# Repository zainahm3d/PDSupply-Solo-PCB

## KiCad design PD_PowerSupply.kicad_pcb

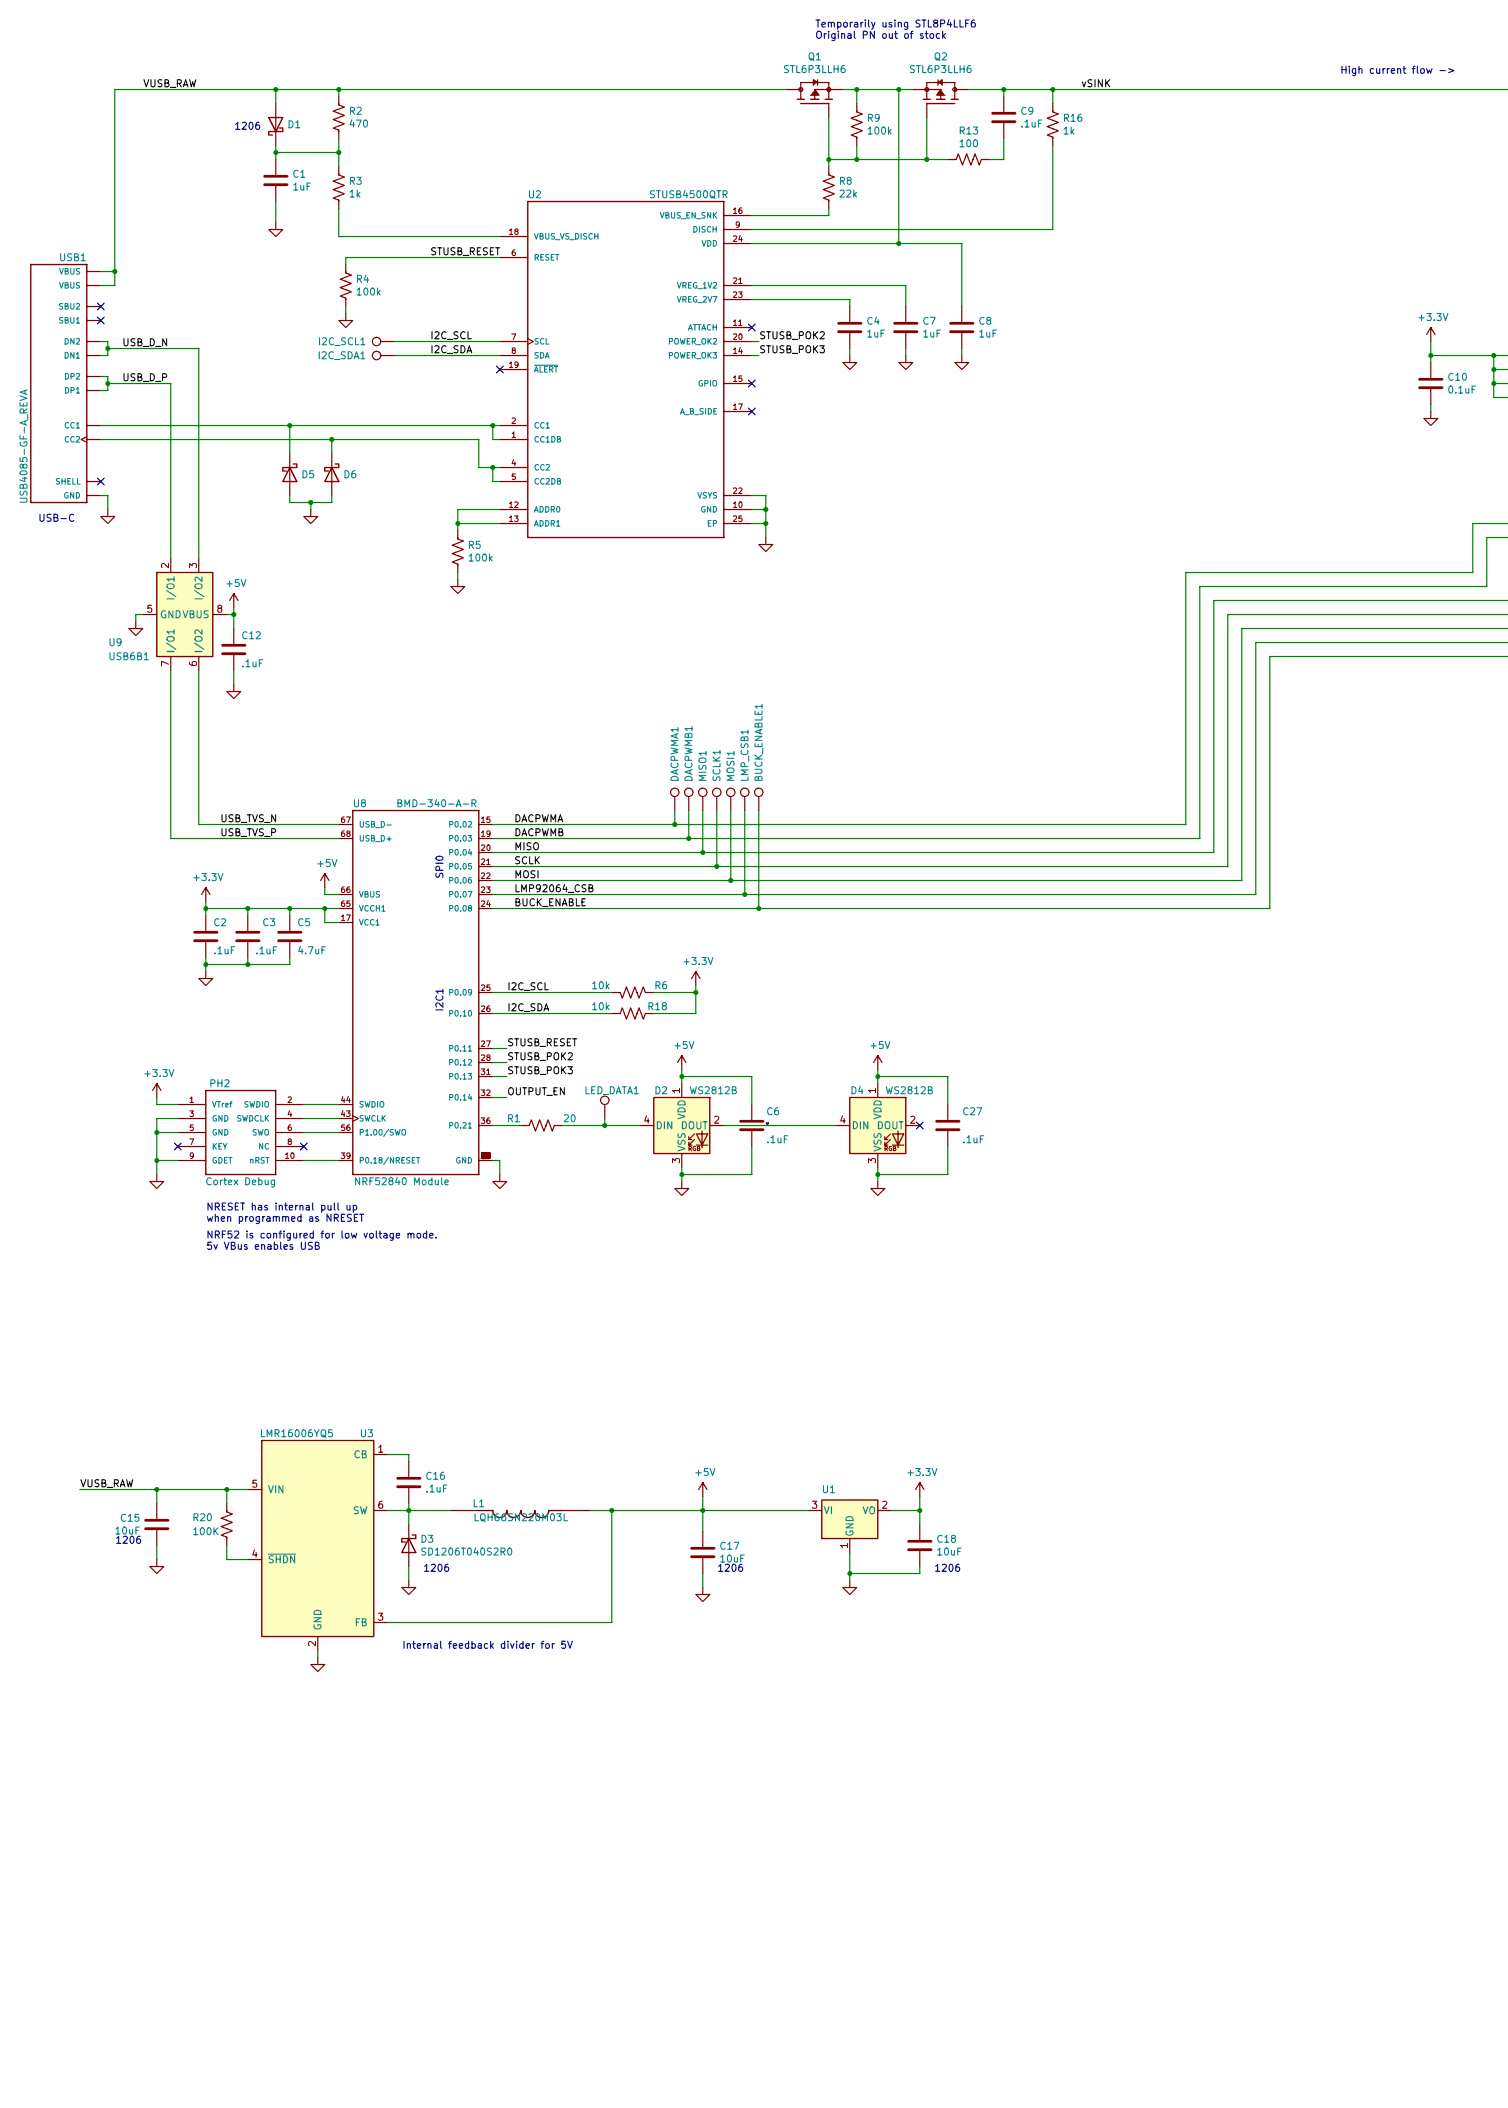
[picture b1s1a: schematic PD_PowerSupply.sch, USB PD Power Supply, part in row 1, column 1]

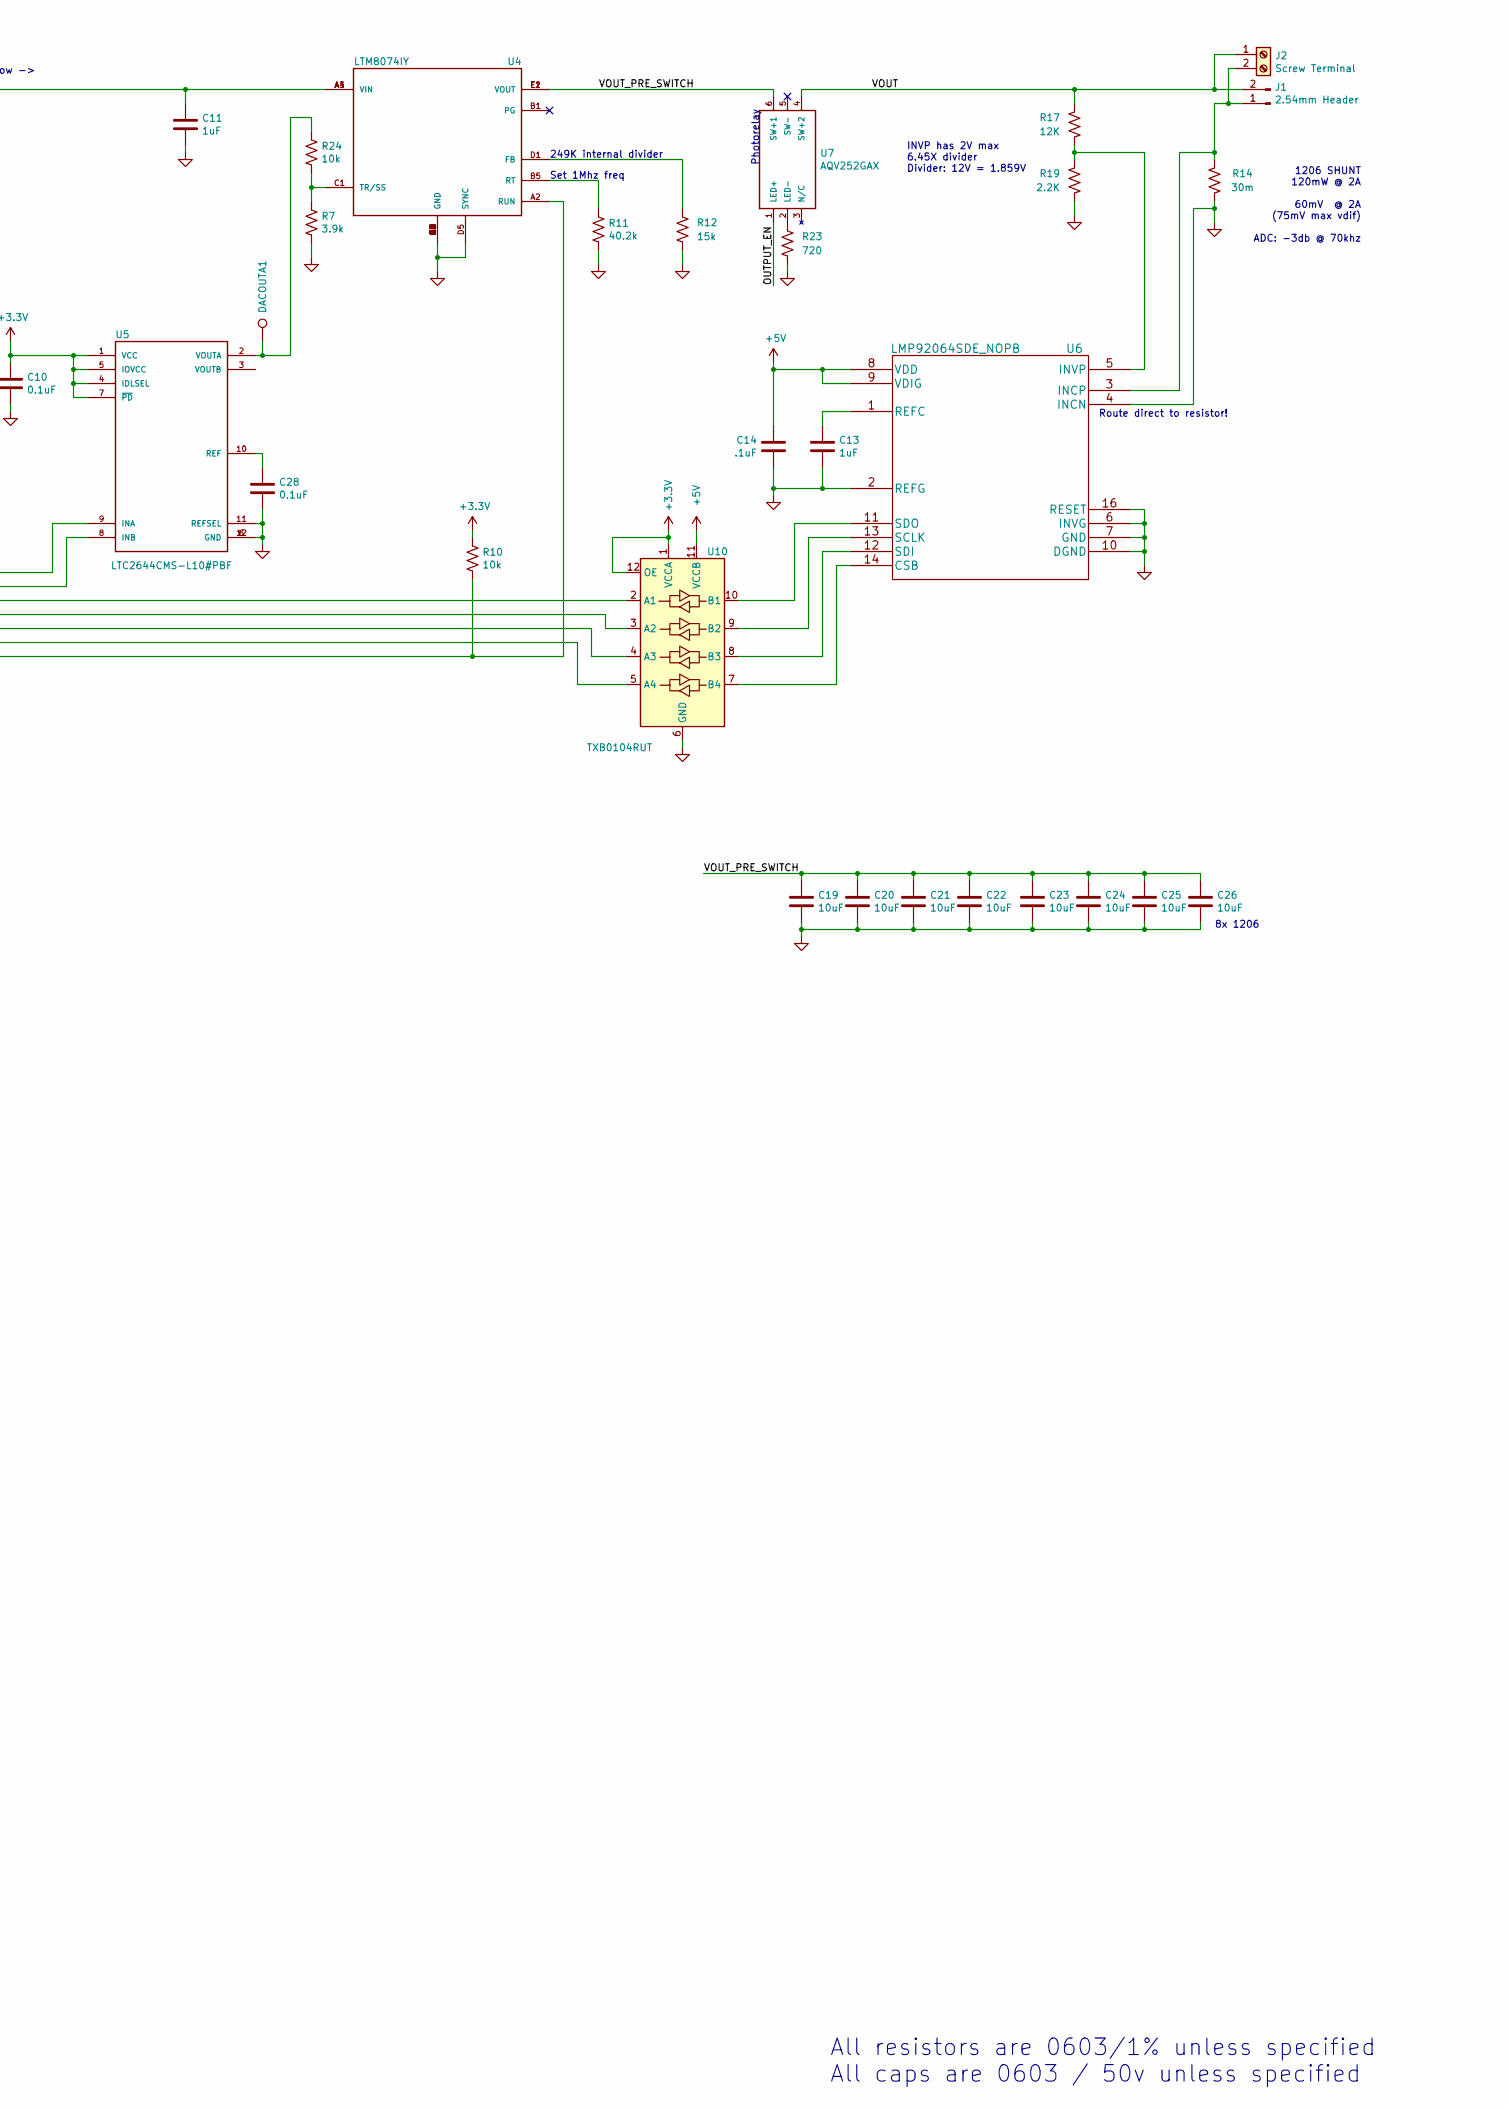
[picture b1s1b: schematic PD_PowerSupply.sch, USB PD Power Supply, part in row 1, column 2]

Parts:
BUCK_ENABLE1: TestPoint; TestPoint_Pad_D1.0mm
C1, C4, C7, C8, C11, C13: 1uF; C_0603_1608Metric
C2, C3, C6, C9, C12, C14, C27: .1uF; C_0603_1608Metric
C5: 4.7uF; C_0603_1608Metric
C10, C28: 0.1uF; C_0603_1608Metric
C15, C17, C18, C19, C20, C21, C22, C23, C24, C25, C26: 10uF; C_1206_3216Metric
C16: .1uF; C_1206_3216Metric
D1: D_Schottky; D_1206_3216Metric_Castellated
D2, D4: WS2812B; LED_WS2812B_PLCC4_5.0x5.0mm_P3.2mm
D3: SD1206T040S2R0; D_1206_3216Metric_Castellated
D5, D6: D_Schottky; D_0603_1608Metric_Castellated
DACOUTA1: TestPoint; TestPoint_Pad_D1.0mm
DACPWMA1: TestPoint; TestPoint_Pad_D1.0mm
DACPWMB1: TestPoint; TestPoint_Pad_D1.0mm
I2C_SCL1, I2C_SDA1: TestPoint; TestPoint_Pad_D1.0mm
J1: 2.54mm Header; PinHeader_1x02_P2.54mm_Horizontal
J2: Screw Terminal; TerminalBlock_Phoenix_MKDS-1,5-2_1x02_P5.00mm_Horizontal
L1: LQH66SN220M03L; IND_LQH66SN220M03L
LED_DATA1: TestPoint; TestPoint_Pad_D1.0mm
LMP_CSB1: TestPoint; TestPoint_Pad_D1.0mm
MISO1: TestPoint; TestPoint_Pad_D1.0mm
MOSI1: TestPoint; TestPoint_Pad_D1.0mm
PH2: FTSH-105-01-L-DV-K; SAMTEC_FTSH-105-01-L-DV-K
Q1, Q2: STL6P3LLH6; TRANS_STL6P3LLH6
R1: 20; R_0603_1608Metric
R2: 470; R_0603_1608Metric
R3, R16: 1k; R_0603_1608Metric
R4, R5, R9: 100k; R_0603_1608Metric
R6, R10, R18, R24: 10k; R_0603_1608Metric
R7: 3.9k; R_0603_1608Metric
R8: 22k; R_0603_1608Metric
R11: 40.2k; R_0603_1608Metric
R12: 15k; R_0603_1608Metric
R13: 100; R_0603_1608Metric
R14: 30m; R_1206_3216Metric
R17: 12K; R_0603_1608Metric
R19: 2.2K; R_0603_1608Metric
R20: 100K; R_0603_1608Metric
R23: 720; R_0603_1608Metric
SCLK1: TestPoint; TestPoint_Pad_D1.0mm
U1: LM1117LD-3.3; SOT-223-3_TabPin2
U2: STUSB4500QTR; QFN50P400X400X90-25N
U3: LMR16006YQ5; SOT-23-6
U4: LTM8074IY; BGA25C65P5X5_400X400X198N
U5: LTC2644CMS-L10#PBF; SOP65P490X110-12N_LTC2644CMS-L10#PBF
U6: LMP92064SDE_NOPB; LMP92064SDE&slash_NOPB
U7: AQV252GAX; SOP6
U8: BMD-340-A-R; RIGADO_BMD-340-A-R
U9: USB6B1; SOIC-8_3.9x4.9mm_P1.27mm
U10: TXB0104RUT; Texas_R_PUQFN-N12
USB1: USB4085-GF-A_REVA; GCT_USB4085-GF-A_REVA

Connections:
+3V3: C2.1, C3.1, C5.1, C10.1, C18.1, PH2.1 (VTref), R6.1, R10.1, R18.1, U1.2 (VO), U5.1 (VCC), U5.4 (IDLSEL), U5.5 (IOVCC), U5.7 (~PD~), U8.17 (VCC1), U8.65 (VCCH1), U10.1 (VCCA), U10.12 (OE)
+5V: C6.1, C12.1, C14.1, C17.1, C27.1, D2.1 (VDD), D4.1 (VDD), L1.2, U1.3 (VI), U3.3 (FB), U6.8 (VDD), U6.9 (VDIG), U8.66 (VBUS), U9.1 (VBUS), U9.8 (VBUS), U10.11 (VCCB)
/BUCK_ENABLE: BUCK_ENABLE1.1, R10.2, U4.A2 (RUN), U8.24 (P0.08)
/DACPWMA: DACPWMA1.1, U5.9 (INA), U8.15 (P0.02)
/DACPWMB: DACPWMB1.1, U5.8 (INB), U8.19 (P0.03)
/I2C_SCL: I2C_SCL1.1, R6.2, U2.7 (SCL), U8.25 (P0.09)
/I2C_SDA: I2C_SDA1.1, R18.2, U2.8 (SDA), U8.26 (P0.10)
/LMP92064_CSB: LMP_CSB1.1, U8.23 (P0.07), U10.5 (A4)
/MISO: MISO1.1, U8.20 (P0.04), U10.2 (A1)
/MOSI: MOSI1.1, U8.22 (P0.06), U10.4 (A3)
/OUTPUT_EN: U7.1 (LED+), U8.32 (P0.14)
/SCLK: SCLK1.1, U8.21 (P0.05), U10.3 (A2)
/STUSB_POK2: U2.20 (POWER_OK2), U8.28 (P0.12)
/STUSB_POK3: U2.14 (POWER_OK3), U8.31 (P0.13)
/STUSB_RESET: R4.1, U2.6 (RESET), U8.27 (P0.11)
/USB_D_N: U9.3 (I/O2), USB1.A7 (DN1), USB1.B7 (DN2)
/USB_D_P: U9.2 (I/O1), USB1.A6 (DP1), USB1.B6 (DP2)
/USB_TVS_N: U8.67 (USB_D-), U9.6 (I/O2)
/USB_TVS_P: U8.68 (USB_D+), U9.7 (I/O1)
/VOUT: J1.2, J2.1, R17.1, U7.4 (SW+2)
/VOUT_PRE_SWITCH: C19.1, C20.1, C21.1, C22.1, C23.1, C24.1, C25.1, C26.1, U4.E1 (VOUT), U4.E2 (VOUT), U7.6 (SW+1)
/VUSB_RAW: C15.2, D1.2 (A), Q1.5_6_7_8 (D), R2.1, R20.1, U3.5 (VIN), USB1.A4 (VBUS), USB1.A9 (VBUS), USB1.B4 (VBUS), USB1.B9 (VBUS)
/vSINK: C9.1, C11.1, Q2.5_6_7_8 (D), R16.2, U4.A3 (VIN), U4.A4 (VIN)
GND: C1.2, C2.2, C3.2, C4.2, C5.2, C6.2, C7.2, C8.2, C10.2, C11.2, C12.2, C13.2, C14.2, C15.1, C17.2, C18.2, C19.2, C20.2, C21.2, C22.2, C23.2, C24.2, C25.2, C26.2, C27.2, C28.2, D2.3 (VSS), D3.2 (A), D4.3 (VSS), D5.2 (A), D6.2 (A), PH2.3 (GND), PH2.5 (GND), PH2.9 (GDET), R4.2, R5.2, R7.2, R11.2, R12.2, R14.2, R19.2, R23.2, U1.1 (GND), U2.10 (GND), U2.22 (VSYS), U2.25 (EP), U3.2 (GND), U4.A1 (GND), U4.A5 (GND), U4.B2 (GND), U4.B3 (GND), U4.B4 (GND), U4.C2 (GND), U4.C3 (GND), U4.C4 (GND), U4.C5 (GND), U4.D2 (GND), U4.D3 (GND), U4.D4 (GND), U4.D5 (SYNC), U4.E3 (GND), U4.E4 (GND), U4.E5 (GND), U5.6 (GND), U5.11 (REFSEL), U5.12 (GND), U6.2 (REFG), U6.4 (INCN), U6.6 (INVG), U6.7 (GND), U6.10 (DGND), U6.16 (RESET), U8.1 (GND), U8.2 (GND), U8.3 (GND), U8.4 (GND), U8.5 (GND), U8.16 (GND), U8.18 (GND), U8.29 (GND), U8.30 (GND), U8.45 (GND), U8.46 (GND), U8.47 (GND), U8.55 (GND), U9.4 (GND), U9.5 (GND), U10.6 (GND), USB1.A1 (GND), USB1.A12 (GND), USB1.B1 (GND), USB1.B12 (GND)
unnamed: C1.1, D1.1 (K), R2.2, R3.1
unnamed: C4.1, U2.23 (VREG_2V7)
unnamed: C7.1, U2.21 (VREG_1V2)
unnamed: C8.1, Q1.1 (S), Q1.2 (S), Q1.3 (S), Q2.1 (S), Q2.2 (S), Q2.3 (S), R9.1, U2.24 (VDD)
unnamed: C9.2, R13.1
unnamed: C13.1, U6.1 (REFC)
unnamed: C16.1, U3.1 (CB)
unnamed: C16.2, D3.1 (K), L1.1, U3.6 (SW)
unnamed: C28.1, U5.10 (REF)
unnamed: D2.2 (DOUT), D4.4 (DIN)
unnamed: D2.4 (DIN), LED_DATA1.1, R1.1
unnamed: D5.1 (K), U2.1 (CC1DB), U2.2 (CC1), USB1.A5 (CC1)
unnamed: D6.1 (K), U2.4 (CC2), U2.5 (CC2DB), USB1.B5 (CC2)
unnamed: DACOUTA1.1, R24.1, U5.2 (VOUTA)
unnamed: J1.1, J2.2, R14.1, U6.3 (INCP)
unnamed: PH2.2 (SWDIO), U8.44 (SWDIO)
unnamed: PH2.4 (SWDCLK), U8.43 (SWCLK)
unnamed: PH2.6 (SWO), U8.56 (P1.00/SWO)
unnamed: PH2.10 (nRST), U8.39 (P0.18/NRESET)
unnamed: Q1.4 (G), Q2.4 (G), R8.1, R9.2, R13.2
unnamed: R1.2, U8.36 (P0.21)
unnamed: R3.2, U2.18 (VBUS_VS_DISCH)
unnamed: R5.1, U2.12 (ADDR0), U2.13 (ADDR1)
unnamed: R8.2, U2.16 (VBUS_EN_SNK)
unnamed: R11.1, U4.B5 (RT)
unnamed: R12.1, U4.D1 (FB)
unnamed: R16.1, U2.9 (DISCH)
unnamed: R17.2, R19.1, U6.5 (INVP)
unnamed: R20.2, U3.4 (~SHDN)
unnamed: R23.1, U7.2 (LED-)
unnamed: R7.1, R24.2, U4.C1 (TR/SS)
unnamed: U6.14 (CSB), U10.7 (B4)
unnamed: U6.12 (SDI), U10.8 (B3)
unnamed: U6.13 (SCLK), U10.9 (B2)
unnamed: U6.11 (SDO), U10.10 (B1)
unnamed: USB1.P1 (SHELL), USB1.P2 (SHELL), USB1.P3 (SHELL), USB1.P4 (SHELL)

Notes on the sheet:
All resistors are 0603/1% unless specified All caps are 0603 / 50v unless specified
1206
High current flow ->
1206 SHUNT 120mW @ 2A 60mV @ 2A (75mV max vdif) ADC: -3db @ 70khz
INVP has 2V max 6.45X divider Divider: 12V = 1.859V
Route direct to resistor!
NRESET has internal pull up when programmed as NRESET
NRF52 is configured for low voltage mode. 5v VBus enables USB
SPI0
I2C1
8x 1206
249K internal divider
Set 1Mhz freq
lol
Photorelay
Temporarily using STL8P4LLF6 Original PN out of stock
Internal feedback divider for 5V
USB-C

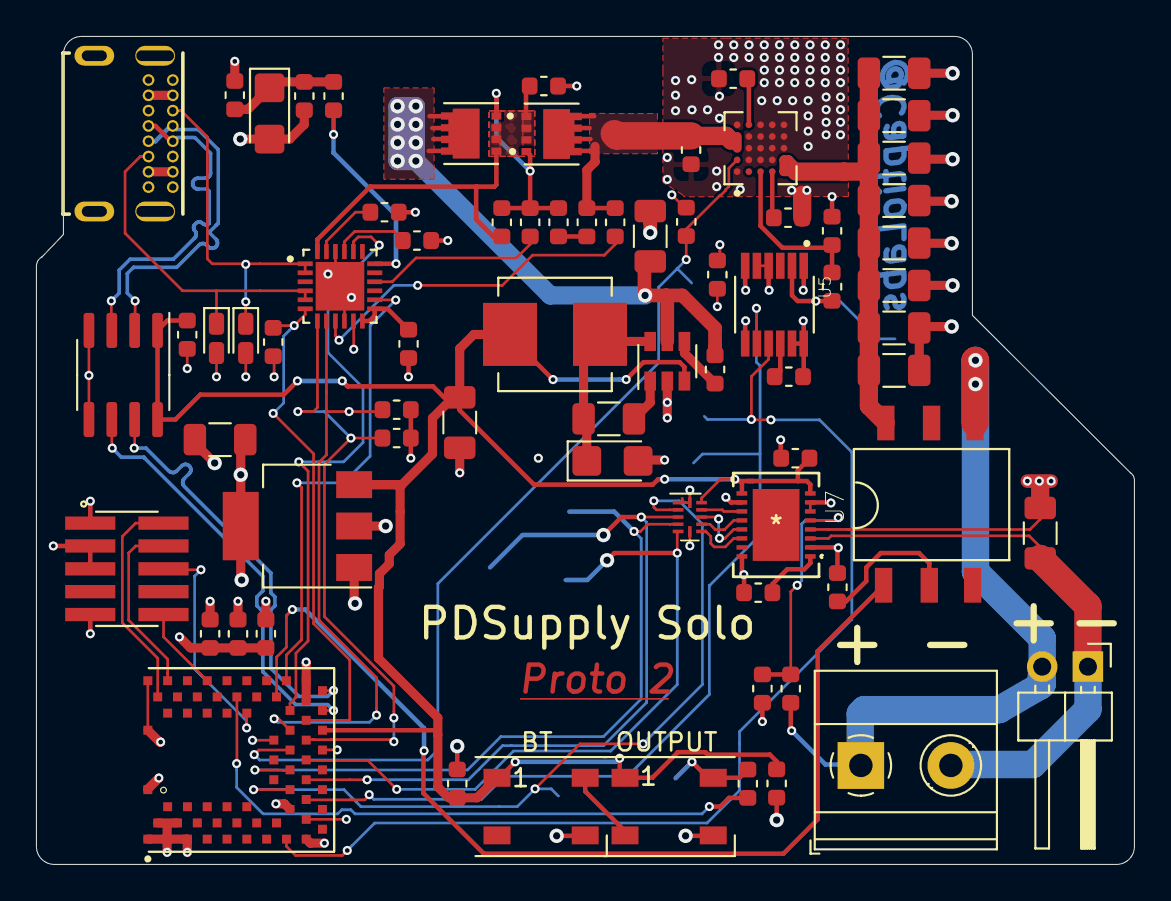
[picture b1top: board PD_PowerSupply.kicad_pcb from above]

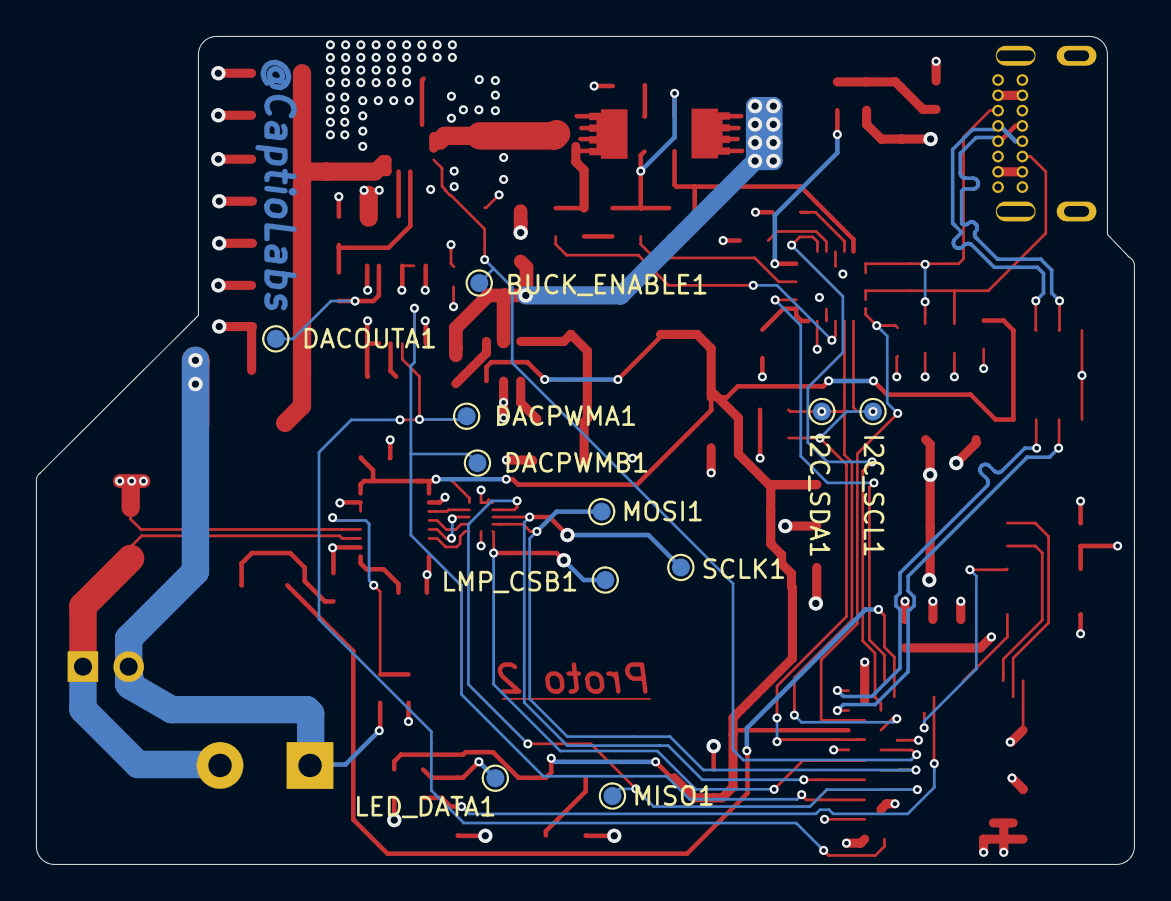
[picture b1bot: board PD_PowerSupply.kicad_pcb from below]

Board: 4 copper layers, 61.0 x 46.0 mm, 83 parts (11 on the bottom side), 60 nets.

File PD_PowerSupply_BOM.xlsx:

PD_PowerSupply
Id | Designator | Package | Quantity | Description/Value | Part Number | Manufacturer | Type
1 | U7 | SOP6 | 1 | SSR Relay | AQV252GAX | Panasonic | SMD
2 | SCLK1,MOSI1,MISO1,LTC_EN1,LTC_CSB1,LMP_CSB1,LED_DATA1,I2C_SDA1,I2C_SCL1 | DNP | 9 | TestPoint | DNP | DNP | SMD
3 | U8 | RIGADO_BMD-340-A-R | 1 | NRF52840 Module | BMD-340-A-R | Rigado/Nordic Semi | SMD
4 | D2,D4 | LED_WS2812B_PLCC4_5.0x5.0mm_P3.2mm | 2 | WS2812B Addressable LED | WS2812B | Worldsemi | SMD
5 | J2 | TerminalBlock_Phoenix_MKDS-1,5-2_1x02_P5.00mm_Horizontal thru hole | 1 | Screw Terminal | 1715721 | Phoenix | Thru Hole
6 | C13,C11,C8,C7,C4,C1 | C_0603_1608Metric | 6 | 1uF 50V ceramic cap | GRT188R61H105KE13D | Murata | SMD
7 | D6,D5 | D_0603_1608Metric_Castellated | 2 | D_Schottky | CD0603-B0340R | Bourns Inc | SMD
8 | C27,C12,C14,C9,C6,C3,C2,C28 | C_0603_1608Metric | 7 | .1uF 50V ceramic cap | C0603C104M5RACTU | kemet | SMD
9 | U9 | SOIC-8_3.9x4.9mm_P1.27mm | 1 | USB TVS Diode | USB6B1 | ST | SMD
10 | R23 | R_0603_1608Metric | 1 | 720 1/16W resistor | RC0603FR-07720RL | Yageo | SMD
11 | C26,C25,C24,C23,C22,C21,C20,C19,C18,C17,C15 | C_1206_3216Metric | 11 | 10uF 25V ceramic cap | C1206C106M3PACTU | Kemet | SMD
12 | U1 | SOT-223-3_TabPin2 | 1 | 3.3V LDO Regulator | LM1117LD-3.3 | TI | SMD
13 | R22 | R_0603_1608Metric | 1 | 10K 1/16W resistor | RC0603JR-0710KL | Yageo | SMD
14 | R21 | R_0603_1608Metric | 1 | 54.9K 1/16W resistor | RC0603FR-0754K9L | Yageo | SMD
15 | R20 | R_0603_1608Metric | 1 | 100K 1/16W resistor | RC0603JR-07100KL | Yageo | SMD
16 | L1 | IND_LQH66SN220M03L | 1 | Inductor 22uH 1.1A 87mOHM | LQH66SN220M03L | Murata | SMD
17 | D3 | D_1206_3216Metric_Castellated | 1 | Diode Schottkey | SD1206T040S2R0 | AVX | SMD
18 | C16 | C_1206_3216Metric | 1 | .1uF 50V ceramic cap | C1206C104M5RACTU | Kemet | SMD
19 | U6 | LMP92064SDE&slash_NOPB | 1 | LMP92064SDE | LMP92064SDE_NOPB | TI | SMD
20 | U5 | LTC2644CMS | 1 | PWM DAC | LTC2644CMS-L10 | Linear technology | SMD
21 | U4 | BGA25C65P5X5_400X400X198N | 1 | Switching power supply | LTM8074IY | Linear technology | SMD
22 | U3 | SOT-23-6 | 1 | Switching power supply | LMR16006YQ5 | TI | SMD
23 | R19 | R_0603_1608Metric | 1 | 2.2K 1/16W resistor | ERJ-3GEYJ222V | Panasonic | SMD
24 | R18,R10,R6 | R_0603_1608Metric | 3 | 10k 1/16W resistor | RC0603JR-0710KL | Yageo | SMD
25 | R17 | R_0603_1608Metric | 1 | 12K 1/16W resistor | RC0603JR-0712KL | Yageo | SMD
26 | R16,R3 | R_0603_1608Metric | 2 | 1k 1/16W resistor | RC0603JR-071KL | Yageo | SMD
27 | R14 | R_1206_3216Metric | 1 | 30m 1/4W resistor | WSL1206R0300FEA18 | Vishay | SMD
28 | R13 | R_0603_1608Metric | 1 | 100 1/16W resistor | RC0603FR-07100RL | Yageo | SMD
29 | R12 | R_0603_1608Metric | 1 | 47K 1/16W resistor | RC0603JR-0747KL | Yageo | SMD
30 | R11 | R_0603_1608Metric | 1 | 40.2k 1/16W resistor | RC0603FR-0740K2L | Yageo | SMD
31 | R9,R5,R4 | R_0603_1608Metric | 3 | 100k 1/16W resistor | RC0603JR-07100KL | Yageo | SMD
32 | R7 | R_0603_1608Metric | 1 | 3.9k 1/16W resistor | TNPW06033K90BEEA |  | SMD
33 | R8 | R_0603_1608Metric | 1 | 22k 1/16W resistor | RC0603JR-0722KL | Yageo | SMD
34 | R2 | R_0603_1608Metric | 1 | 470 1/16W resistor | RC0603FR-07470RL | Yageo | SMD
35 | R1 | R_0603_1608Metric | 1 | 20 1/16W resistor | RC0603FR-0720RL | Yageo | SMD
36 | R24 | R_0603_1608Metric | 1 | 10k 1/16W resistor | MCT0603MD1002DP500 |  | SMD
37 | PH2 | SAMTEC_FTSH-105-01-L-DV-K | 1 | JTAG Connector 10 pin | FTSH-105-01-L-DV-K | SAMTEC | SMD
38 | D1 | D_1206_3216Metric_Castellated | 1 | D_Schottky | SD1206S040S1R0 | AVX | SMD
39 | C10 | C_0603_1608Metric | 1 | 0.1uF 50V ceramic cap | C0603C104M5RACTU | Kemet | SMD
40 | C5 | C_0603_1608Metric | 1 | 4.7uF 10V ceramic cap | C0603C475M8PACTU | Kemet | SMD
41 | J1 | PinHeader_1x02_P2.54mm_Horizontal thru hole | 1 | 2.54mm Header MALE | M20-9960245 | Harwin | Thru Hole
42 | USB1 | GCT_USB4085-GF-A_REVA thru hole | 1 | Female USB 2.0 type C Port | USB4085-GF-A_REVA | GCT_USB4085-GF-A_REVA | Thru Hole
43 | U2 | QFN50P400X400X90-25N | 1 | USB PD controller | STUSB4500QTR | ST | SMD
44 | Q2,Q1 | TRANS_STL6P3LLH6 | 2 | MOSFET P CHANNEL | STL8P4LLF6 | ST | SMD

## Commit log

2020-03-22 STUSB config done
2020-03-23 switched to linear chip
2020-03-23 switched to unswitched
2020-03-29 added footprints and symbol for LTC2972
2020-03-30 set up coprocessor
2020-04-03 integrated STM32 and assigned most footprints
2020-04-03 added debug and power out connectors
2020-04-03 added secondary 2.54 headers
2020-04-04 started routing switchers
2020-04-04 power stage in progress
2020-04-05 power stage complete, STUSB in progress
2020-04-05 STUSB in progress
2020-04-06 STM32 in progress
2020-04-24 changed testpoints
2020-04-24 create single channel version w LTC7106-1 SPI DAC
2020-05-10 Setup LMP92064
    Wanted to avoid using the internal ADC in the nrf52
2020-05-10 Correct reference ground connection
2020-05-10 Added BMD-340 standalone NRF52840
    Low voltage mode + usb support
2020-05-10 add power rails, photorelay, bulk caps
2020-05-10 Filled voltage divider values
2020-05-11 set feedback resistance and noted vout accuracy
2020-05-16 Added USB protection diodes
2020-05-16 Added in capacitor for diode protection
2020-05-26 Started routing process, swapped out photorelay for an SMD alternative
2020-05-26 completed routing. Ready for eval.
2020-05-27 Fixed DRC errors, moved silkscreen
2020-05-27 Setup fab drawing and remove designators from silk
2020-05-28 Generated gerbers, started BOM setup for PCBWay
2020-05-29 Generate gerbers, drill, centroid, and BOM
2020-05-29 Regenerate Gerbers
2020-05-31 Create LICENSE
2020-06-15 Switched to PWM DAC
2020-06-18 Added level shifter for ADC
2020-06-18 Added missing SPI test points (oops)
2020-08-13 after testing, removed FB resistors and backup PWM DAC channel
2020-10-17 remove feedback divider from 5V buck (internal divider)
2022-03-03 [WIP] fixing voltage leakage on USB C port
